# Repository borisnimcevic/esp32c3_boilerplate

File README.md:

# ESP32-C3 minimum components to start a project

### Motivation:
The plan is to copy this project every time a new project based on the esp32c3 starts.

### TODO:
* make a script for renaming all the relevant files for KiCAD to the name of the project
* Update the Bill Of materials

### Bill Of Materials
|Component  |Quantity |Link   |
|-----      |-----    |-----  |
|ESP32-C3   |1        |[digikey](https://www.digikey.se/en/products/detail/espressif-systems/ESP32-C3/14115579) |
|or with embedded flash (ESP32-C3FN4)   |1        |[digikey](https://www.digikey.se/en/products/detail/espressif-systems/ESP32-C3FN4/14115581) |
|FLASH 4MBIT   |1        |[digikey](https://www.digikey.se/en/products/detail/winbond-electronics/W25Q16JVSSIM/12143335) |
|resistor 100 0402   |7        |[digikey](https://www.digikey.se/en/products/detail/yageo/RC0402FR-07100RP/4935263) |
|resistor 10k 0402   |1        |[digikey](https://www.digikey.se/en/products/detail/yageo/RC0402FR-0710KP/4935264) |
|LED red 0603|30        |[digikey](https://www.digikey.se/en/products/detail/osram-opto-semiconductors-inc/LS-Q976-NR-1/1227986) |
|LED transistor driver |4        |[digikey](https://www.digikey.se/en/products/detail/micro-commercial-co/MMBT5550-TP/10054662) |
|Ceramic antenna (chip antenna)|1        |[digikey](https://www.digikey.se/en/products/detail/johanson-technology-inc/2450AT18A100E/1560676) |
|Ceramic capacitor 1pF |1        |[digikey](https://www.digikey.se/en/products/detail/johanson-technology-inc/500R07S1R0BV4T/1561521?s=N4IgTCBcDaIKwAYECUEHYDKBGVAhAagCwAqIAugL5A) |
|Ceramic capacitor 10nF |1        |[digikey](https://www.digikey.se/en/products/detail/tdk-corporation/CGA2B2X5R1E103M050BA/3949410) |
|Ceramic capacitor 100nF |1        |[digikey](https://www.digikey.se/en/products/detail/tdk-corporation/CGA2B1X7R1C104M050BC/3949478) |
|Ceramic capacitor 1uF |1        |[digikey](https://www.digikey.se/en/products/detail/kyocera-avx/04023D105KAT2A/13557232) |
|Ceramic capacitor 4.7uF |1        |[digikey](https://www.digikey.se/en/products/detail/yageo/CC0402KRX5R5BB475/7164360) |
|Ceramic inductor 2.7nH |1        |[digikey](https://www.digikey.se/en/products/detail/johanson-technology-inc/L-07C2N7SV6T/1830166?s=N4IgTCBcDaIDIFoAMB2AwmAcigygNQDYAVEAXQF8g) |
|Ceramic inductor 3.9nH |1        |[digikey](https://www.digikey.se/en/products/detail/johanson-technology-inc/L-07C3N9SV6T/1915227) |
|Ceramic inductor 39nH |1        |[digikey](https://www.digikey.se/en/products/detail/johanson-technology-inc/L-07C39NJV6T/1915226) |

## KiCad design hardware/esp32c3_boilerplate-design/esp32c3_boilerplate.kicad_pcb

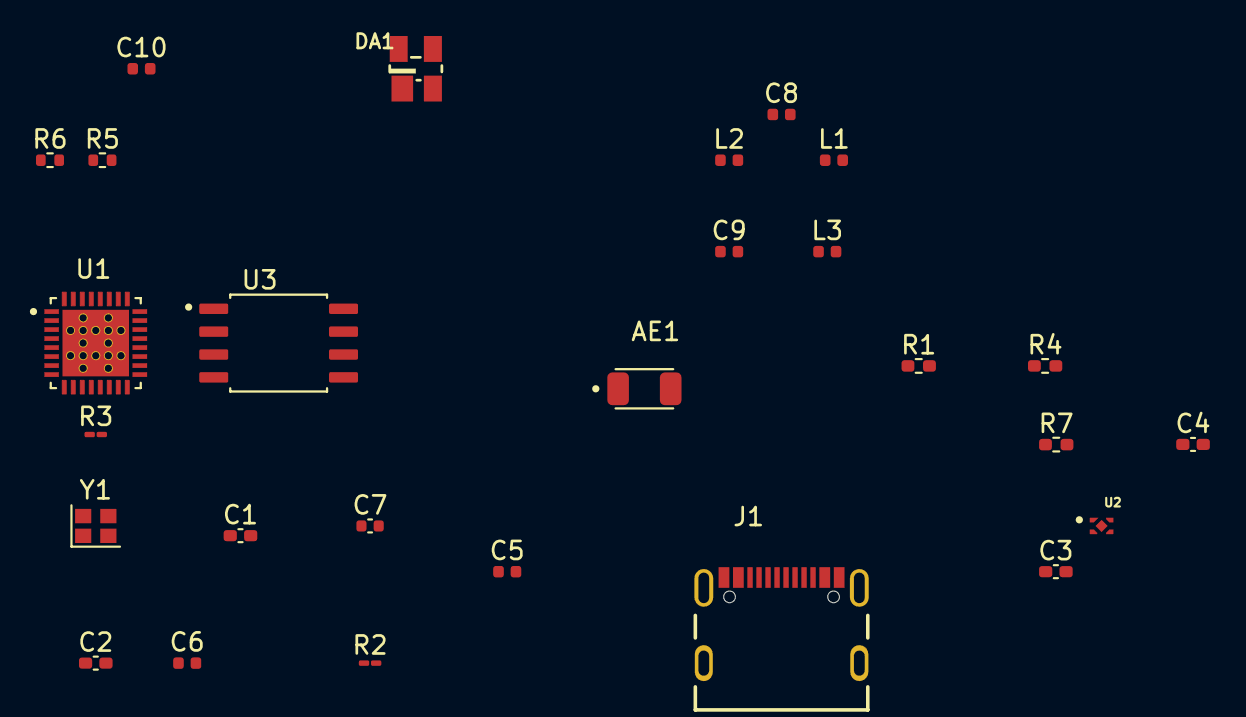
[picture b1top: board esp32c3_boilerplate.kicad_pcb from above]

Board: 2 copper layers, 27 parts (0 on the bottom side), 22 nets, no tracks yet.

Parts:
AE1: 2450AT18A100E; ANTC3216X140N
C1, C2: 8pF; C_0402_1005Metric_Pad0.74x0.62mm_HandSolder
C3, C4: 2.2uF; C_0402_1005Metric_Pad0.74x0.62mm_HandSolder
C5: 4.7uF; L_0402_1005Metric
C6, C8: 100nF; L_0402_1005Metric
C7: 1pF; C_0402_1005Metric
C9: 1uF; L_0402_1005Metric
C10: 10nF; L_0402_1005Metric
DA1: SR05; SOT143
J1: USB4105-GF-A; GCT_USB4105-GF-A
L1: 2.7 nH; L_0402_1005Metric
L2: 3.9 nH; L_0402_1005Metric
L3: 39nH; L_0402_1005Metric
R1, R4: 5.1k 1%; R_0402_1005Metric_Pad0.72x0.64mm_HandSolder
R2: 0; R_01005_0402Metric_Pad0.57x0.30mm_HandSolder
R3: 10k; R_01005_0402Metric_Pad0.57x0.30mm_HandSolder
R5, R6: 10k; R_0402_1005Metric
R7: 10k; R_0402_1005Metric_Pad0.72x0.64mm_HandSolder
U1: ESP32-C3FH4; QFN50P500X500X90-33N
U2: MIC5524-3.3YMT-TZ; VREG_MIC5524-3.3YMT-TZ
U3: W25Q16JVSSIQ; SOIC127P790X216-8N
Y1: 40MHz; Crystal_SMD_2016-4Pin_2.0x1.6mm

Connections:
+3.3VA: C9.1, C10.1, L3.2, U1.2 (VDD3P3), U1.3 (VDD3P3), U1.31 (VDDA), U1.32 (VDDA)
+3V3: C4.1, C5.1, C6.1, C8.1, L3.1, R3.1, R5.2, R6.2, U1.11 (VDD3P3_RTC), U1.17 (VDD3P3_CPU), U2.1 (VOUT), U3.8 (VCC)
+5V: C3.1, DA1.4, J1.A4_B9 (VBUS), J1.B4_A9 (VBUS), R7.1, U2.4 (VIN)
CS-memory: U1.21 (SPICS0), U3.1 (~CS)
DI-memory: U1.23 (SPID), U3.5 (DI(IO0))
DO-memory: U1.24 (SPIQ), U3.2 (DO(IO1))
GND: C1.2, C2.2, C3.2, C4.2, C5.2, C6.2, C8.2, C9.2, C10.2, DA1.1, J1.A1_B12 (GND), J1.B1_A12 (GND), J1.S1 (SHELL_GND), J1.S2 (SHELL_GND), J1.S3 (SHELL_GND), J1.S4 (SHELL_GND), L1.1, R1.1, R4.2, U1.33 (GND), U2.2 (GND), U2.EP (EXP), U3.4 (GND), Y1.2, Y1.4
GPIO2_STRAP: R6.1, U1.6 (GPIO2)
GPIO8_STRAP: R5.1, U1.14 (GPIO8)
unnamed: AE1.1, L2.2
unnamed: C2.1, R2.1, Y1.3
unnamed: C7.2, L1.2, L2.1
unnamed: J1.A5 (CC1), R1.2
unnamed: J1.B5 (CC2), R4.1
unnamed: R3.2, U1.7 (CHIP_EN)
unnamed: R7.2, U2.3 (EN)
SPICLK-memory: U1.22 (SPICLK), U3.6 (CLK)
USB_D+: DA1.3, J1.A6 (DP1), J1.B6 (DP2), U1.26 (GPIO19)
USB_D-: DA1.2, J1.A7 (DN1), J1.B7 (DN2), U1.25 (GPIO18)
XTAL_N: R2.2, U1.29 (XTAL_N)
XTAL_P: C1.1, U1.30 (XTAL_P), Y1.1
antenna: C7.1, U1.1 (LNA_IN)

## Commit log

2022-06-19 Init repo
2022-06-19 Made a "TODO" list in README.
2022-06-19 Relinked the libraries.
